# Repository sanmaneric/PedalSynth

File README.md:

<h1 align="center">
  :notes: SynthBuddy :notes:
</h1>

<h2 align="center">
  A combination digital and analog synthesizer with integrated speaker amplifier.
</h2>

<div align="center">

</div>

# PCB Designs
We have two KiCad projects in this repo. One for the Class-D Amp Dev Board (ordered week 2), and one for our project design. The naming of the KiCad project of the Dev Board is a misnomer.
 - [Amplifier Dev Board](https://github.com/sanmaneric/PedalSynth/tree/main/Electrical%20Design/PedalSynth)
 - [SynthBuddy Board](https://github.com/sanmaneric/PedalSynth/tree/main/Electrical%20Design/Modules/ECE%20411%20Project)

# Authors
PedalSynth is developed by Eric Sanman, Sierra Buckley, Chris Crider, and Chuong Vo as part of ECE411 at <a href="https://pdx.edu/engineering" style="color: green; text-decoration: underline;text-decoration-style: dotted;">Portland State University</a>
.

# License
SynthBuddy is licensed under a GNU/GPL v3 license.

# View Key Deliverables
Things Andrew would want to look at:
 - :white_check_mark: [View PDS](https://github.com/sanmaneric/PedalSynth/blob/main/Product%20Development/ProductDescriptionSpecification-Team8.rev1.2.pdf)
 - :date: [Browse Weekly Progress Reports](https://github.com/sanmaneric/PedalSynth/blob/main/Weekly%20Progress%20Reports/Weekly%20Progress%20Report.md)
  - :camera: [Progress Photos & Videos](https://github.com/sanmaneric/PedalSynth/tree/main/Weekly%20Progress%20Reports/Progresss%20Photos)
  - :date: [View Gantt Chart](https://github.com/sanmaneric/PedalSynth/blob/main/Gantt%20Chart/ECE%20411%20PWM%20Hybrid%20Synth%20Pedal.pdf)
 - :technologist: [View Code](https://github.com/sanmaneric/PedalSynth/tree/main/Programming)
 - :white_check_mark: [View KiCad PDF Exports](https://github.com/sanmaneric/PedalSynth/tree/main/Electrical%20Design/Docs)

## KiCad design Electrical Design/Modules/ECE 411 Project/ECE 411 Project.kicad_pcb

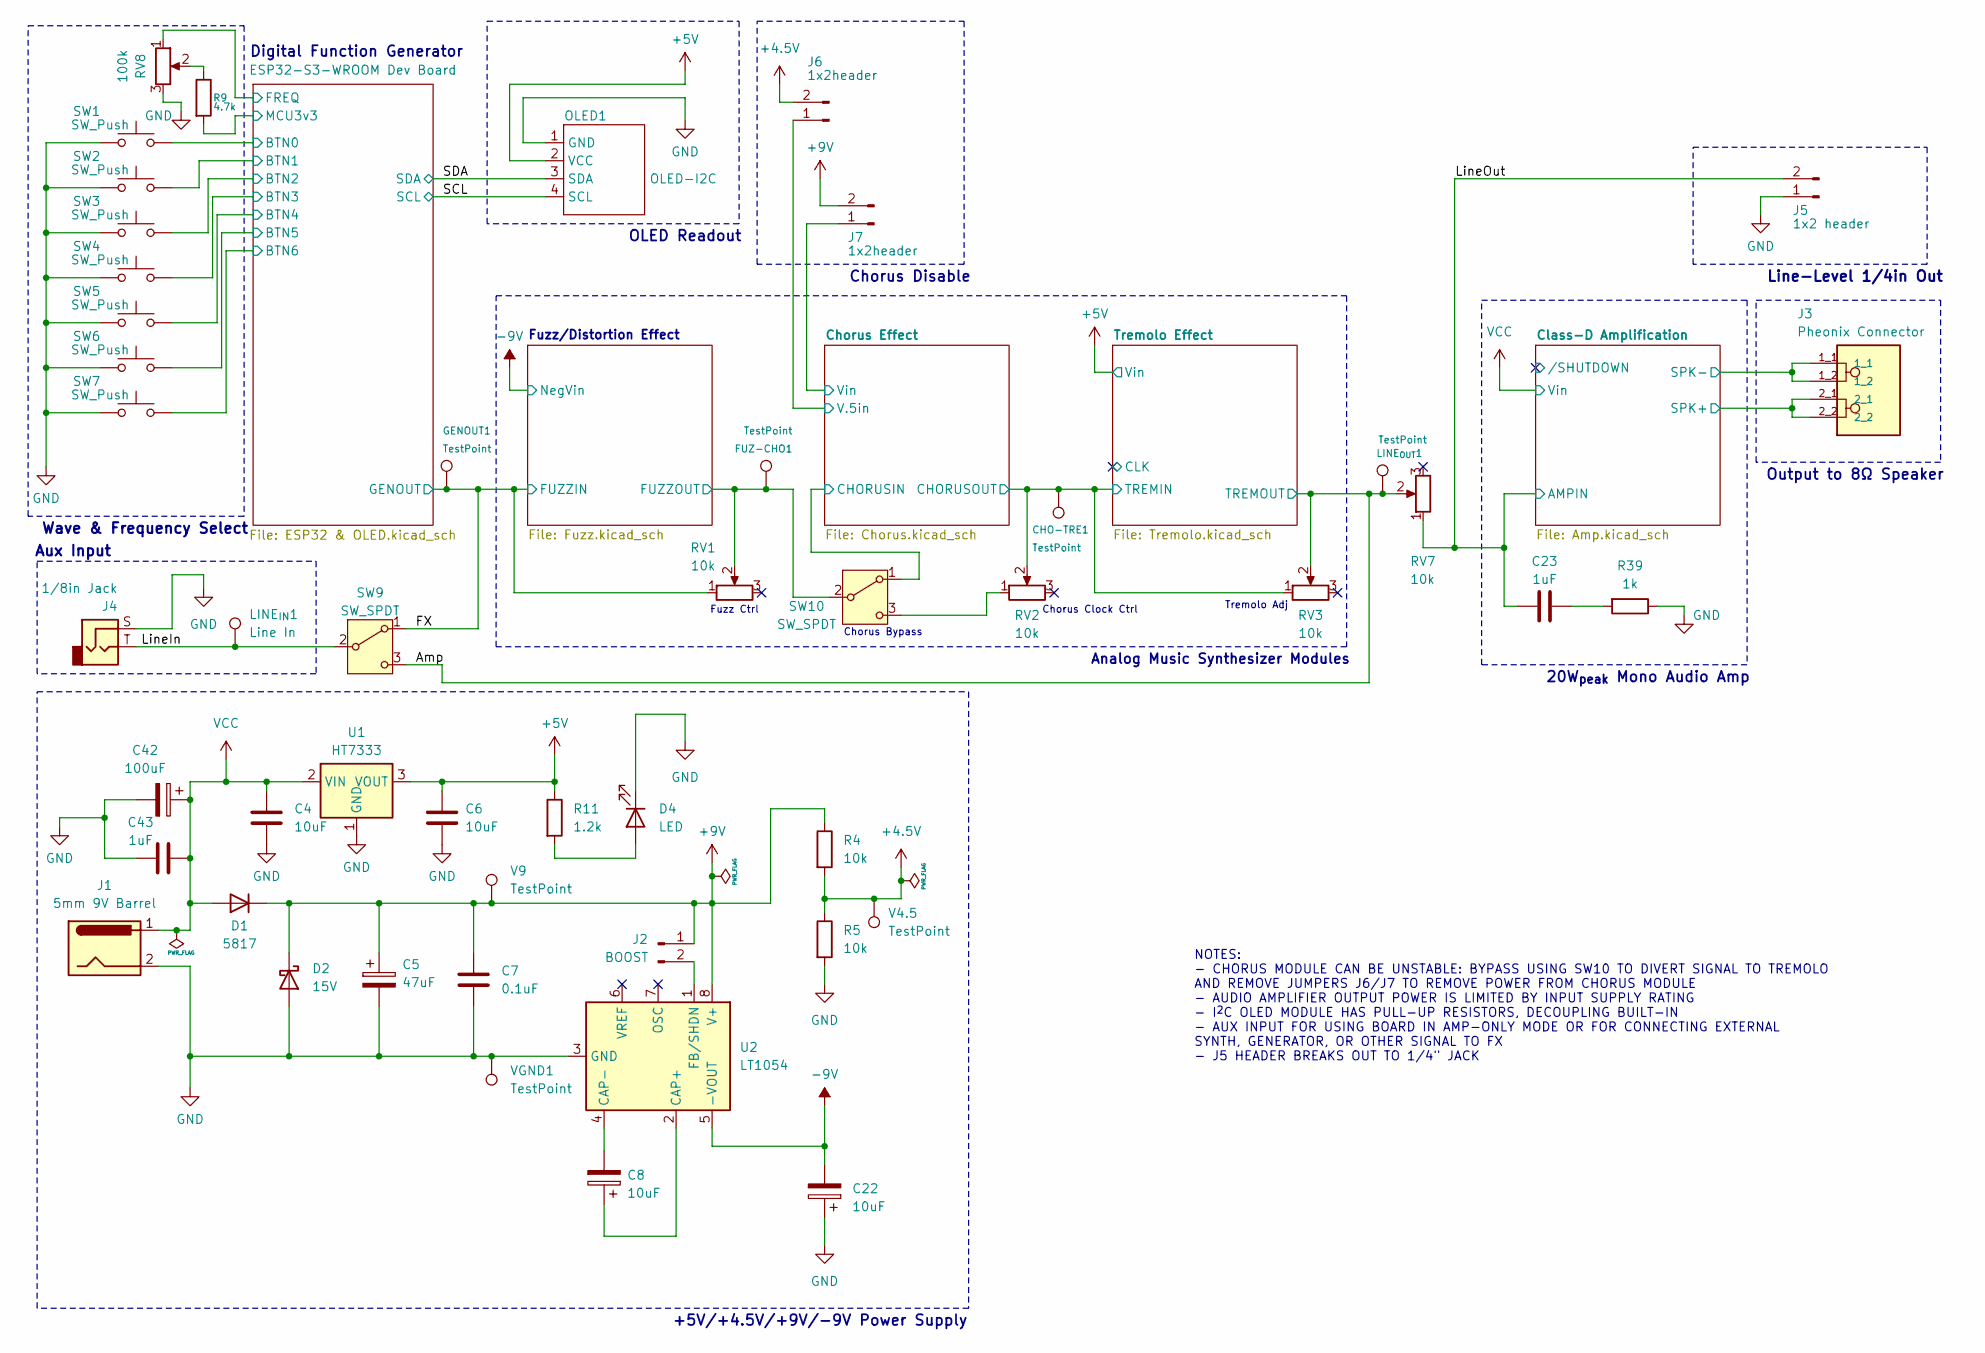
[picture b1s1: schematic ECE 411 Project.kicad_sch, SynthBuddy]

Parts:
C4, C6: 10uF; C_1206_3216Metric_Pad1.33x1.80mm_HandSolder; Part_Number CL31B106KAHNFNE
C5: 47uF; CP_Radial_D8.0mm_P3.50mm; Part_Number UVK2A470MPD
C7: 0.1uF; C_0805_2012Metric_Pad1.18x1.45mm_HandSolder; Part_Number CL21B104KCFNNNE
C8: 10uF; CP_Radial_D8.0mm_P3.50mm; Part_Number UVR2C100MPD
C22: 10uF; CP_Radial_D7.5mm_P2.50mm; Part_Number UVR2C100MPD
C23: 1uF; C_0805_2012Metric_Pad1.18x1.45mm_HandSolder; Part_Origin DK
C42: 100uF; CP_Radial_D8.0mm_P3.50mm; Part_Origin DK
C43: 1uF; C_0805_2012Metric_Pad1.18x1.45mm_HandSolder; Part_Number CL21B104KBCNNNC
CHO-TRE1: TestPoint; TestPoint_Loop_D3.80mm_Drill2.5mm
D1: 5817; D_0805_2012Metric_Pad1.15x1.40mm_HandSolder; Part_Origin DK
D2: 15V; D_DO-41_SOD81_P10.16mm_Horizontal; Part_Origin DK
D4: LED; LED_D5.0mm
FUZ-CHO1: TestPoint; TestPoint_Loop_D3.80mm_Drill2.5mm
GENOUT1: TestPoint; TestPoint_Loop_D3.80mm_Drill2.5mm
J1: 5mm 9V Barrel; BarrelJack_Horizontal
J2: BOOST; PinHeader_1x02_P2.54mm_Vertical
J3: Pheonix Connector; PHOENIX_1190297; PARTREV 03.11.2020
J4: 1/8in Jack; Jack_3.5mm_CUI_SJ-3523-SMT_Horizontal
J5: 1x2 header; PinSocket_1x02_P2.54mm_Vertical
J6, J7: 1x2header; PinSocket_1x02_P2.54mm_Vertical
LINE_{IN}1: Line In; TestPoint_Loop_D3.80mm_Drill2.5mm
LINE_{OUT}1: TestPoint; TestPoint_Loop_D3.80mm_Drill2.5mm
OLED1: OLED-I2C; PinHeader_1x04_P2.54mm_Vertical
R4, R5: 10k; R_0805_2012Metric_Pad1.20x1.40mm_HandSolder; Part_Origin DK
R9: 4.7k; R_0805_2012Metric_Pad1.20x1.40mm_HandSolder
R11: 1.2k; R_0805_2012Metric_Pad1.20x1.40mm_HandSolder
R39: 1k; R_0805_2012Metric_Pad1.20x1.40mm_HandSolder; Part_Origin DK
RV1, RV2, RV3: 10k; PinSocket_1x02_P2.54mm_Vertical; Part_Origin AMZ
RV7: 10k; PinSocket_1x02_P2.54mm_Vertical; Part_Origin DK
RV8: 100k; PinSocket_1x03_P2.54mm_Vertical; Part_Origin AMZ
SW1, SW2, SW3, SW4, SW5, SW6, SW7: SW_Push; PinHeader_1x02_P2.54mm_Vertical; Part_Origin TAYDA
SW9, SW10: SW_SPDT; SW_Slide_SPDT_Angled_CK_OS102011MA1Q
U1: HT7333; SOT-89-3; Part_Origin SBP
U2: LT1054; CERDIP-8_W7.62mm_SideBrazed; Part_Origin SBP
V4.5, V9: TestPoint; TestPoint_Loop_D3.80mm_Drill2.5mm
VGND1: TestPoint; TestPoint_Loop_D3.80mm_Drill2.5mm

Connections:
+4.5V: J6.2, R4.2, R5.1, V4.5.1
+5V: C6.1, OLED1.2 (VCC), R11.1, U1.3 (VOUT); also elsewhere on the board
+9V: C5.1, C7.1, D1.1 (K), D2.1 (K), J2.1, J7.2, R4.1, U2.8 (V+), V9.1
-9V: C22.2, U2.5 (-VOUT); also elsewhere on the board
/Amp: LINE_{OUT}1.1, RV3.2, RV7.2, SW9.3 (C); also elsewhere on the board
/Chorus Effect/CHORUSIN: SW10.1 (A); also elsewhere on the board
/Chorus Effect/CHORUSOUT: CHO-TRE1.1, RV2.2, RV3.1; also elsewhere on the board
/Chorus Effect/V.5in: J6.1; also elsewhere on the board
/Chorus Effect/Vin: J7.1; also elsewhere on the board
/Class-D Amplification/SPK+: J3.2_1, J3.2_2; also elsewhere on the board
/Class-D Amplification/SPK-: J3.1_1, J3.1_2; also elsewhere on the board
/ESP32-S3-WROOM Dev Board/BTN0: SW1.2; also elsewhere on the board
/ESP32-S3-WROOM Dev Board/BTN1: SW2.2; also elsewhere on the board
/ESP32-S3-WROOM Dev Board/BTN2: SW3.2; also elsewhere on the board
/ESP32-S3-WROOM Dev Board/BTN3: SW4.2; also elsewhere on the board
/ESP32-S3-WROOM Dev Board/BTN4: SW5.2; also elsewhere on the board
/ESP32-S3-WROOM Dev Board/BTN5: SW6.2; also elsewhere on the board
/ESP32-S3-WROOM Dev Board/BTN6: SW7.2; also elsewhere on the board
/ESP32-S3-WROOM Dev Board/FREQ: RV8.1; also elsewhere on the board
/ESP32-S3-WROOM Dev Board/MCU3v3: R9.2; also elsewhere on the board
/FX: GENOUT1.1, RV1.1, SW9.1 (A); also elsewhere on the board
/Fuzz Schematic/FUZZOUT: FUZ-CHO1.1, RV1.2, SW10.2 (B); also elsewhere on the board
/LineIn: J4.T, LINE_{IN}1.1, SW9.2 (B)
/LineOut: C23.1, J5.2, RV7.1; also elsewhere on the board
/SCL: OLED1.4 (SCL); also elsewhere on the board
/SDA: OLED1.3 (SDA); also elsewhere on the board
GND: C4.2, C5.2, C6.2, C7.2, C22.1, C42.2, C43.1, D2.2 (A), D4.1 (K), J1.2, J4.S, J5.1, OLED1.1 (GND), R5.2, R39.1, RV8.3, SW1.1, SW2.1, SW3.1, SW4.1, SW5.1, SW6.1, SW7.1, U1.1 (GND), U2.3 (GND), VGND1.1; also elsewhere on the board
unnamed: C23.2, R39.2
unnamed: D4.2 (A), R11.2
unnamed: J2.2, U2.1 (FB/SHDN)
unnamed: R9.1, RV8.2
unnamed: RV2.1, SW10.3 (C)
unnamed: C8.1, U2.2 (CAP+)
unnamed: C8.2, U2.4 (CAP-)
Vin: C4.1, C42.1, C43.2, D1.2 (A), J1.1, U1.2 (VIN); also elsewhere on the board

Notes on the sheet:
Output to 8Ω Speaker
20W_{peak} Mono Audio Amp
Chorus Disable
Analog Music Synthesizer Modules
Fuzz Ctrl
Line-Level 1/4in Out
+5V/+4.5V/+9V/-9V Power Supply
Digital Function Generator
Chorus Clock Ctrl
OLED Readout
Tremolo Adj
Wave & Frequency Select
Aux Input
Chorus Bypass
Fuzz/Distortion Effect
NOTES: - CHORUS MODULE CAN BE UNSTABLE: BYPASS USING SW10 TO DIVERT SIGNAL TO TREMOLO AND REMOVE JUMPERS J6/J7 TO REMOVE POWER FROM CHORUS MODULE - AUDIO AMPLIFIER OUTPUT POWER IS LIMITED BY INPUT SUPPLY RATING - I^{2}C OLED MODULE HAS PULL-UP RESISTORS, DECOUPLING BUILT-IN - AUX INPUT FOR USING BO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

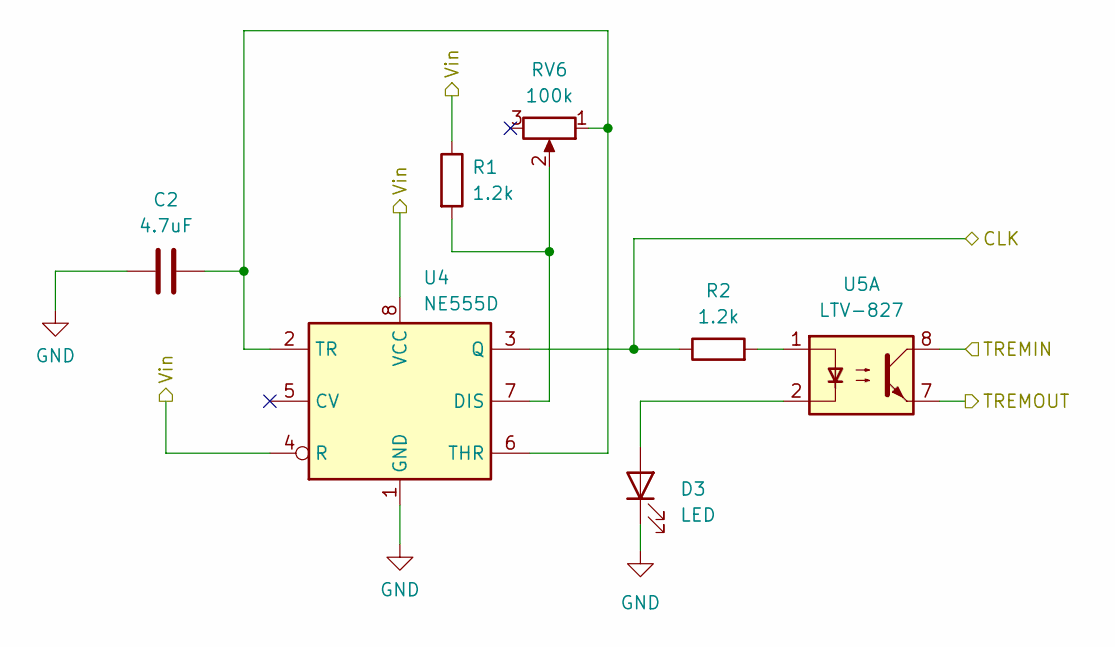
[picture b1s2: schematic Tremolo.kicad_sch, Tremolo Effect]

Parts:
C2: 4.7uF; C_1206_3216Metric_Pad1.33x1.80mm_HandSolder; Part_Number CL31B475KAHNNNE
D3: LED; LED_D5.0mm; Part_Origin DK
R1, R2: 1.2k; R_0805_2012Metric_Pad1.20x1.40mm_HandSolder; Part_Origin DK
RV6: 100k; PinSocket_1x02_P2.54mm_Vertical; Part_Origin DK
U4: NE555D; SOIC-8_3.9x4.9mm_P1.27mm; Part_Origin DK
U5: LTV-827; DIP-8_W7.62mm; Part_Origin SBP

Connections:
+5V: R1.1, U4.4 (R), U4.8 (VCC); also elsewhere on the board
/Amp: U5.7; also elsewhere on the board
/Chorus Effect/CHORUSOUT: U5.8; also elsewhere on the board
/Tremolo Effect/CLK: R2.1, U4.3 (Q)
GND: C2.1, D3.1 (K), U4.1 (GND); also elsewhere on the board
unnamed: D3.2 (A), U5.2
unnamed: R2.2, U5.1
unnamed: R1.2, RV6.2, U4.7 (DIS)
unnamed: C2.2, RV6.1, U4.2 (TR), U4.6 (THR)

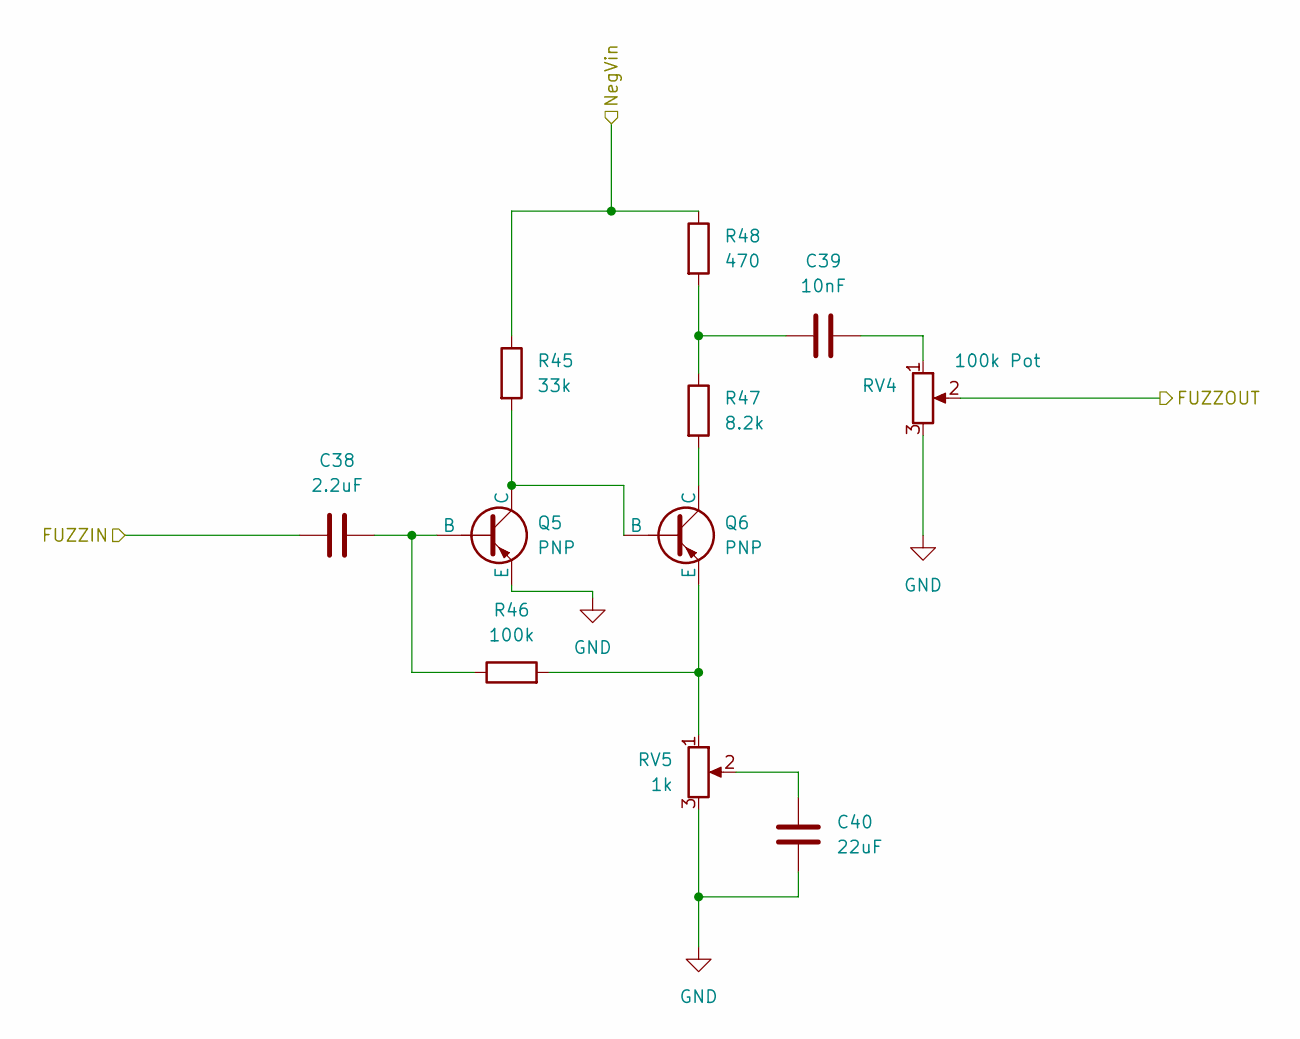
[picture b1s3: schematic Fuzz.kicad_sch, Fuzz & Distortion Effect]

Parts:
C38: 2.2uF; C_0805_2012Metric_Pad1.18x1.45mm_HandSolder; Part_Origin DK
C39: 10nF; C_0805_2012Metric_Pad1.18x1.45mm_HandSolder; Part_Origin DK
C40: 22uF; C_1206_3216Metric_Pad1.33x1.80mm_HandSolder; Part_Origin DK
Q5, Q6: PNP; TO-52-3
R45: 33k; R_0805_2012Metric_Pad1.20x1.40mm_HandSolder; Part_Origin DK
R46: 100k; R_0805_2012Metric_Pad1.20x1.40mm_HandSolder; Part_Origin DK
R47: 8.2k; R_0805_2012Metric_Pad1.20x1.40mm_HandSolder; Part_Origin DK
R48: 470; R_0805_2012Metric_Pad1.20x1.40mm_HandSolder; Part_Origin DK
RV4: 100k Pot; PinHeader_1x03_P2.54mm_Vertical; Part_Origin AMZ
RV5: 1k; PinSocket_1x03_P2.54mm_Vertical; Part_Origin AMZ

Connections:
-9V: R45.1, R48.1; also elsewhere on the board
/FX: C38.1; also elsewhere on the board
/Fuzz Schematic/FUZZOUT: RV4.2; also elsewhere on the board
GND: C40.1, Q5.3 (E), RV4.3, RV5.3; also elsewhere on the board
unnamed: C39.1, R47.1, R48.2
unnamed: C39.2, RV4.1
unnamed: C40.2, RV5.2
unnamed: C38.2, Q5.2 (B), R46.1
unnamed: Q5.1 (C), Q6.2 (B), R45.2
unnamed: Q6.1 (C), R47.2
unnamed: Q6.3 (E), R46.2, RV5.1

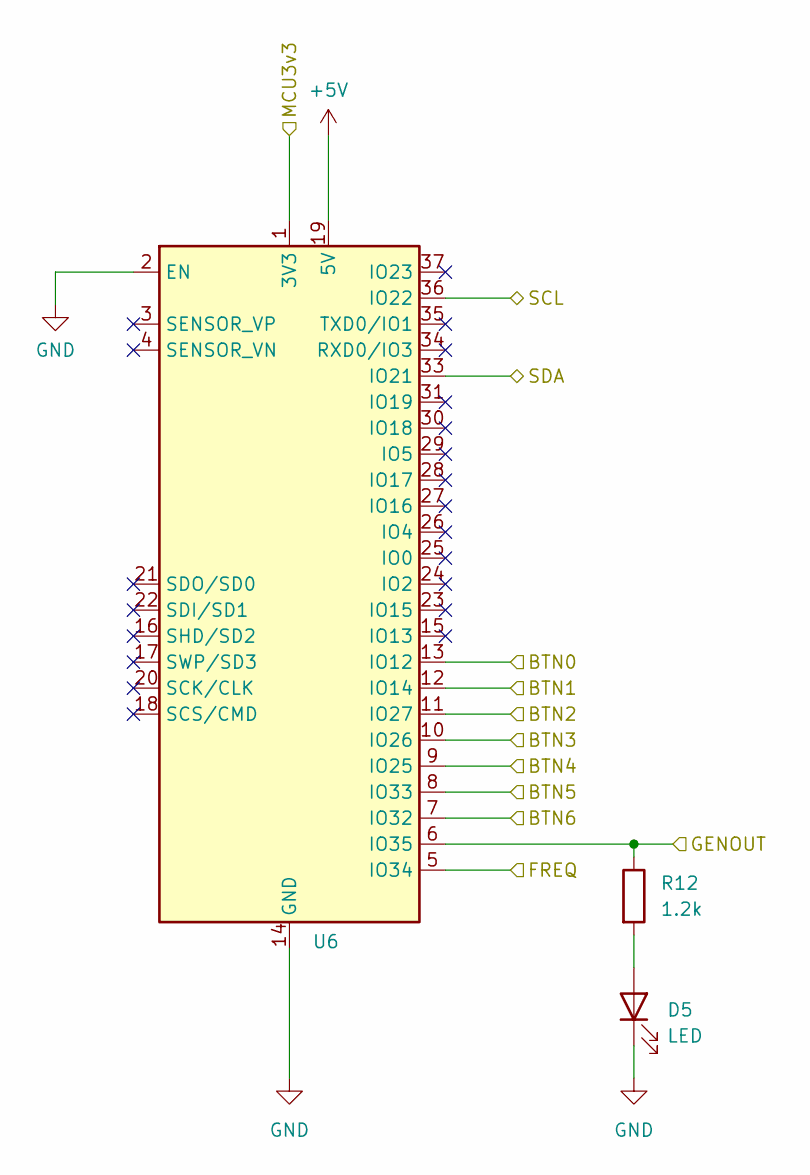
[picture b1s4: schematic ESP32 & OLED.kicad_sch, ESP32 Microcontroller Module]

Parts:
D5: LED; LED_D5.0mm
R12: 1.2k; R_0805_2012Metric_Pad1.20x1.40mm_HandSolder
U6: PinHeader_ESP32_WROOM_Narrow

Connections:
+5V: U6.19 (5V); also elsewhere on the board
/ESP32-S3-WROOM Dev Board/BTN0: U6.13 (IO12); also elsewhere on the board
/ESP32-S3-WROOM Dev Board/BTN1: U6.12 (IO14); also elsewhere on the board
/ESP32-S3-WROOM Dev Board/BTN2: U6.11 (IO27); also elsewhere on the board
/ESP32-S3-WROOM Dev Board/BTN3: U6.10 (IO26); also elsewhere on the board
/ESP32-S3-WROOM Dev Board/BTN4: U6.9 (IO25); also elsewhere on the board
/ESP32-S3-WROOM Dev Board/BTN5: U6.8 (IO33); also elsewhere on the board
/ESP32-S3-WROOM Dev Board/BTN6: U6.7 (IO32); also elsewhere on the board
/ESP32-S3-WROOM Dev Board/FREQ: U6.5 (IO34); also elsewhere on the board
/ESP32-S3-WROOM Dev Board/MCU3v3: U6.1 (3V3); also elsewhere on the board
/FX: R12.1, U6.6 (IO35); also elsewhere on the board
/SCL: U6.36 (IO22); also elsewhere on the board
/SDA: U6.33 (IO21); also elsewhere on the board
GND: D5.1 (K), U6.2 (EN), U6.14 (GND), U6.15 (GND), U6.38 (GND), U6.39 (GND); also elsewhere on the board
unnamed: D5.2 (A), R12.2

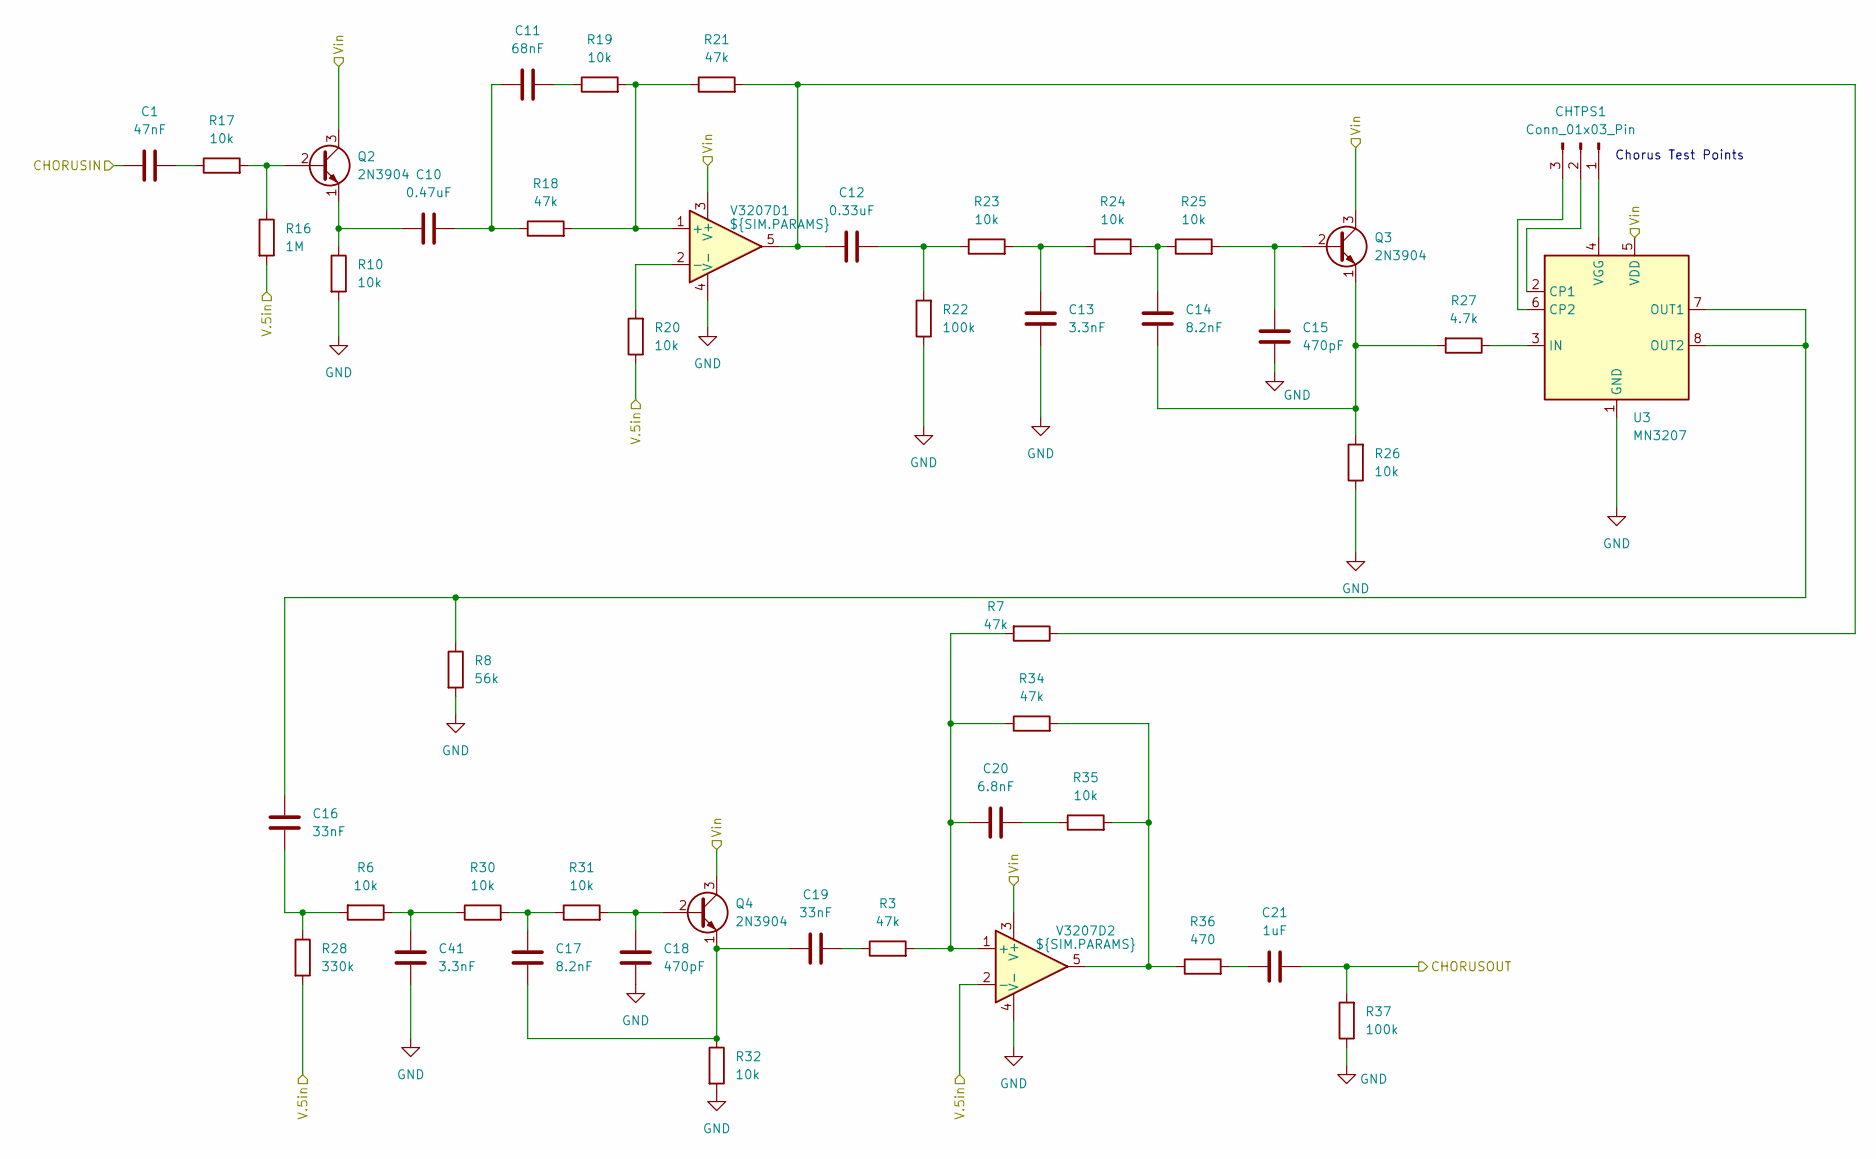
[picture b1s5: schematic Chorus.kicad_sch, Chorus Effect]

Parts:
C1: 47nF; C_0805_2012Metric_Pad1.18x1.45mm_HandSolder; Part_Number CL21B473KBCNNNC
C10: 0.47uF; C_0805_2012Metric_Pad1.18x1.45mm_HandSolder; Part_Number CL21B473KBCNNNC
C11: 68nF; C_0805_2012Metric_Pad1.18x1.45mm_HandSolder; Part_Number KGM21NR71H683KT
C12: 0.33uF; C_0805_2012Metric_Pad1.18x1.45mm_HandSolder; Part_Number CL21B334KBFNNNE
C13, C41: 3.3nF; C_0805_2012Metric_Pad1.18x1.45mm_HandSolder; Part_Number C0805C332K1RECAUTO
C14, C17: 8.2nF; C_0805_2012Metric_Pad1.18x1.45mm_HandSolder; Part_Number C0402C822K1RACAUTO
C15, C18: 470pF; C_0805_2012Metric_Pad1.18x1.45mm_HandSolder; Part_Number C0805C471K5RAC7800
C16, C19: 33nF; C_0805_2012Metric_Pad1.18x1.45mm_HandSolder; Part_Number C0805C333K1RECAUTO
C20: 6.8nF; C_0805_2012Metric_Pad1.18x1.45mm_HandSolder; Part_Number C0805C682J1GEC7210
C21: 1uF; C_0805_2012Metric_Pad1.18x1.45mm_HandSolder; Part_Number CL21B104KBCNNNC
CHTPS1: Conn_01x03_Pin; PinSocket_1x03_P2.54mm_Vertical
Q2, Q3, Q4: 2N3904; TO-92_Inline
R3, R7, R18, R21, R34: 47k; R_0805_2012Metric_Pad1.20x1.40mm_HandSolder; Part_Origin DK
R6, R10, R17, R19, R20, R23, R24, R25, R26, R30, R31, R32, R35: 10k; R_0805_2012Metric_Pad1.20x1.40mm_HandSolder; Part_Origin DK
R8: 56k; R_0805_2012Metric_Pad1.20x1.40mm_HandSolder; Part_Origin DK
R16: 1M; R_0805_2012Metric_Pad1.20x1.40mm_HandSolder; Part_Origin DK
R22, R37: 100k; R_0805_2012Metric_Pad1.20x1.40mm_HandSolder; Part_Origin DK
R27: 4.7k; R_0805_2012Metric_Pad1.20x1.40mm_HandSolder; Part_Origin DK
R28: 330k; R_0805_2012Metric_Pad1.20x1.40mm_HandSolder; Part_Origin DK
R36: 470; R_0805_2012Metric_Pad1.20x1.40mm_HandSolder; Part_Origin DK
U3: MN3207; CERDIP-8_W7.62mm_SideBrazed; Part_Origin SBP
V3207D1, V3207D2: ${SIM.PARAMS}; CERDIP-8_W7.62mm_SideBrazed; Part_Number IC-400-1033

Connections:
/Chorus Effect/CHORUSIN: C1.1; also elsewhere on the board
/Chorus Effect/CHORUSOUT: C21.2, R37.2; also elsewhere on the board
/Chorus Effect/V.5in: R16.2, R20.1, R28.2, V3207D2.2 (-); also elsewhere on the board
/Chorus Effect/Vin: Q2.3 (C), Q3.3 (C), Q4.3 (C), U3.5 (VDD), V3207D1.3 (V+), V3207D2.3 (V+); also elsewhere on the board
GND: C13.1, C15.1, C18.1, C41.2, R8.2, R10.2, R22.1, R26.1, R32.2, R37.1, U3.1 (GND), V3207D1.4 (V-), V3207D2.4 (V-); also elsewhere on the board
unnamed: C1.2, R17.1
unnamed: C10.2, C11.1, R18.1
unnamed: C11.2, R19.1
unnamed: C12.1, R7.1, R21.2, V3207D1.5
unnamed: C12.2, R22.2, R23.1
unnamed: C13.2, R23.2, R24.1
unnamed: C14.2, R24.2, R25.1
unnamed: C16.2, R6.2, R28.1
unnamed: C17.2, R30.2, R31.1
unnamed: C19.2, R3.1
unnamed: C20.2, R35.1
unnamed: C21.1, R36.2
unnamed: C41.1, R6.1, R30.1
unnamed: CHTPS1.1, U3.4 (VGG)
unnamed: CHTPS1.2, U3.2 (CP1)
unnamed: CHTPS1.3, U3.6 (CP2)
unnamed: Q2.2 (B), R16.1, R17.2
unnamed: C10.1, Q2.1 (E), R10.1
unnamed: C15.2, Q3.2 (B), R25.2
unnamed: C14.1, Q3.1 (E), R26.2, R27.2
unnamed: C18.2, Q4.2 (B), R31.2
unnamed: C17.1, C19.1, Q4.1 (E), R32.1
unnamed: R34.2, R35.2, R36.1, V3207D2.5
unnamed: R27.1, U3.3 (IN)
unnamed: C16.1, R8.1, U3.7 (OUT1), U3.8 (OUT2)
unnamed: R18.2, R19.2, R21.1, V3207D1.1 (+)
unnamed: R20.2, V3207D1.2 (-)
unnamed: C20.1, R3.2, R7.2, R34.1, V3207D2.1 (+)

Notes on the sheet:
Chorus Test Points

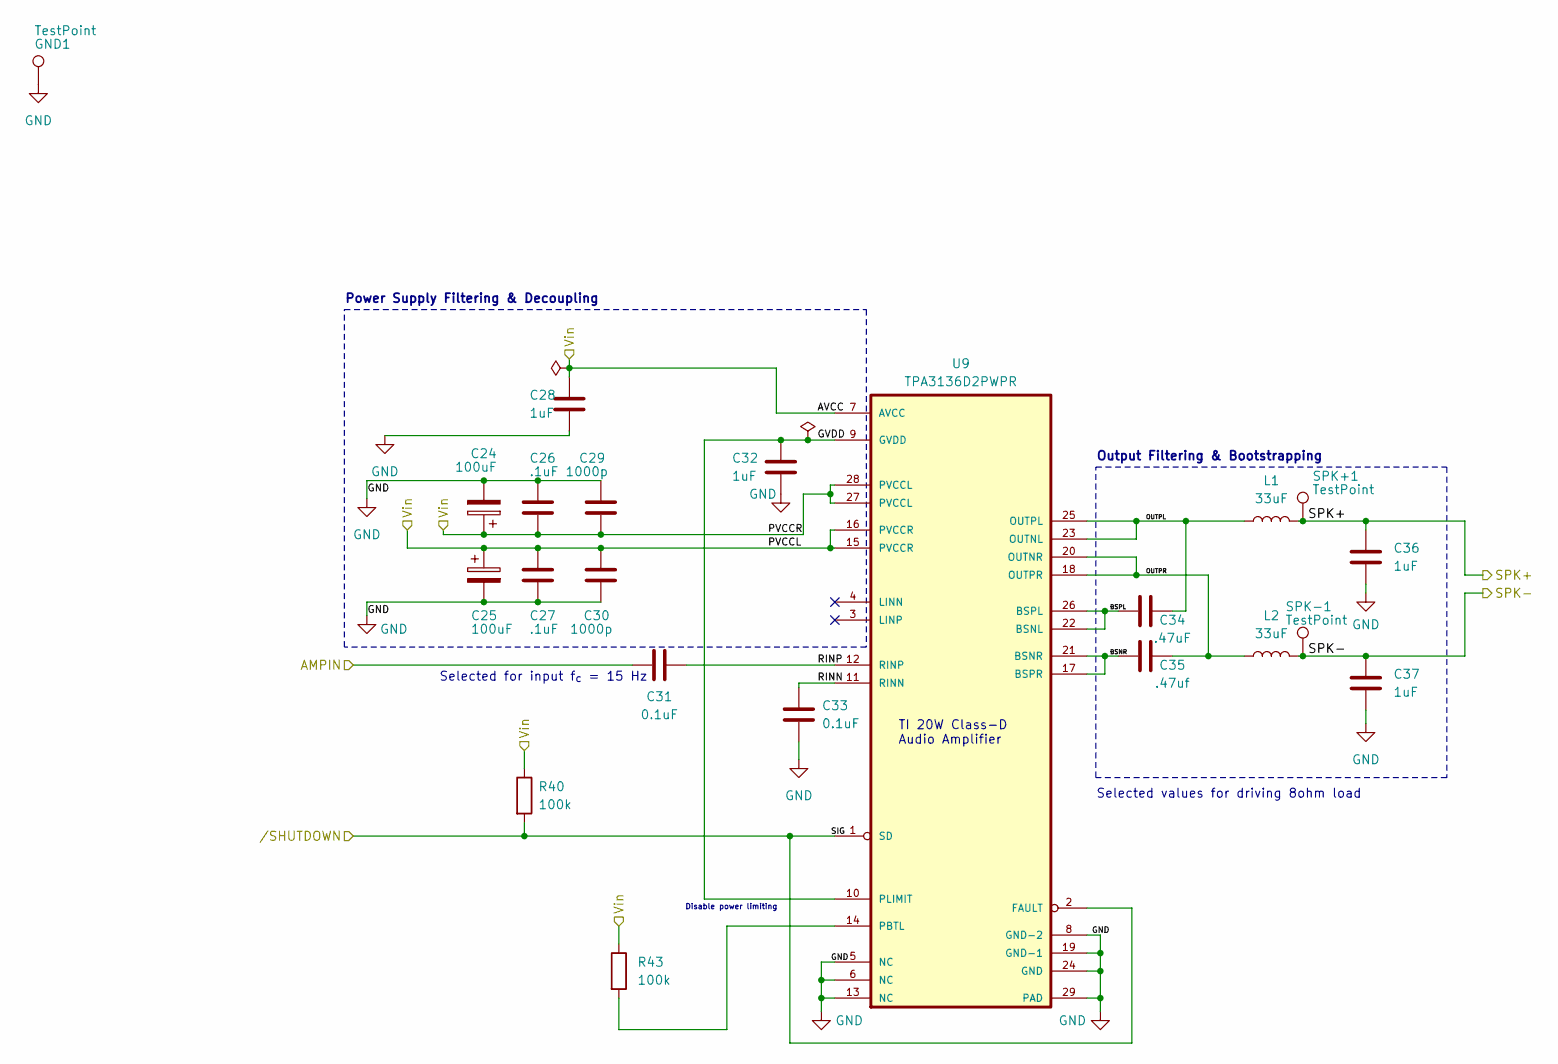
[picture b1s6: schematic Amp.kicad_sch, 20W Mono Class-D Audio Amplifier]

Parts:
C24, C25: 100uF; CP_Radial_D8.0mm_P3.50mm; Part_Origin DK
C26, C27: .1uF; C_0805_2012Metric_Pad1.18x1.45mm_HandSolder; Part_Origin DK
C28, C32, C36, C37: 1uF; C_0805_2012Metric_Pad1.18x1.45mm_HandSolder; Part_Origin DK
C29, C30: 1000p; C_0805_2012Metric_Pad1.18x1.45mm_HandSolder; Part_Origin DK
C31, C33: 0.1uF; C_0805_2012Metric_Pad1.18x1.45mm_HandSolder; Part_Origin DK
C34: .47uF; C_0805_2012Metric_Pad1.18x1.45mm_HandSolder; Part_Number 1276-1074-1-ND
C35: .47uf; C_0805_2012Metric_Pad1.18x1.45mm_HandSolder; Part_Number 1276-1074-1-ND
GND1: TestPoint; TestPoint_Loop_D3.80mm_Drill2.5mm; Part_Origin DK
L1, L2: 33uF; RL110-330K-RC
R40, R43: 100k; R_0805_2012Metric_Pad1.20x1.40mm_HandSolder; Part_Origin DK
SPK+1: TestPoint; TestPoint_Loop_D3.80mm_Drill2.5mm; Part_Origin DK
SPK-1: TestPoint; TestPoint_Loop_D3.80mm_Drill2.5mm; Part_Origin DK
U9: TPA3136D2PWPR; IC_TPS61196PWPRQ1; Part_Origin SBP

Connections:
/Class-D Amplification/BSNR: C35.1, U9.17 (BSPR), U9.21 (BSNR)
/Class-D Amplification/BSPL: C34.1, U9.22 (BSNL), U9.26 (BSPL)
/Class-D Amplification/GVDD: C32.2, U9.9 (GVDD), U9.10 (PLIMIT)
/Class-D Amplification/OUTPL: C34.2, L1.1, U9.23 (OUTNL), U9.25 (OUTPL)
/Class-D Amplification/OUTPR: C35.2, L2.1, U9.18 (OUTPR), U9.20 (OUTNR)
/Class-D Amplification/RINN: C33.1, U9.11 (RINN)
/Class-D Amplification/RINP: C31.1, U9.12 (RINP)
/Class-D Amplification/SIG: R40.2, U9.1 (SD), U9.2 (FAULT)
/Class-D Amplification/SPK+: C36.1, L1.2, SPK+1.1; also elsewhere on the board
/Class-D Amplification/SPK-: C37.1, L2.2, SPK-1.1; also elsewhere on the board
/LineOut: C31.2; also elsewhere on the board
GND: C24.2, C25.2, C26.1, C27.2, C28.2, C29.1, C30.2, C32.1, C33.2, C36.2, C37.2, GND1.1, U9.5 (NC), U9.6 (NC), U9.8 (GND-2), U9.13 (NC), U9.19 (GND-1), U9.24 (GND), U9.29 (PAD); also elsewhere on the board
unnamed: R43.2, U9.14 (PBTL)
Vin: C24.1, C25.1, C26.2, C27.1, C28.1, C29.2, C30.1, R40.1, R43.1, U9.7 (AVCC), U9.15 (PVCCR), U9.16 (PVCCR), U9.27 (PVCCL), U9.28 (PVCCL); also elsewhere on the board

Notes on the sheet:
TI 20W Class-D Audio Amplifier
Output Filtering & Bootstrapping
Selected for input f_{c} = 15 Hz
Disable power limiting
Selected values for driving 8ohm load
Power Supply Filtering & Decoupling
